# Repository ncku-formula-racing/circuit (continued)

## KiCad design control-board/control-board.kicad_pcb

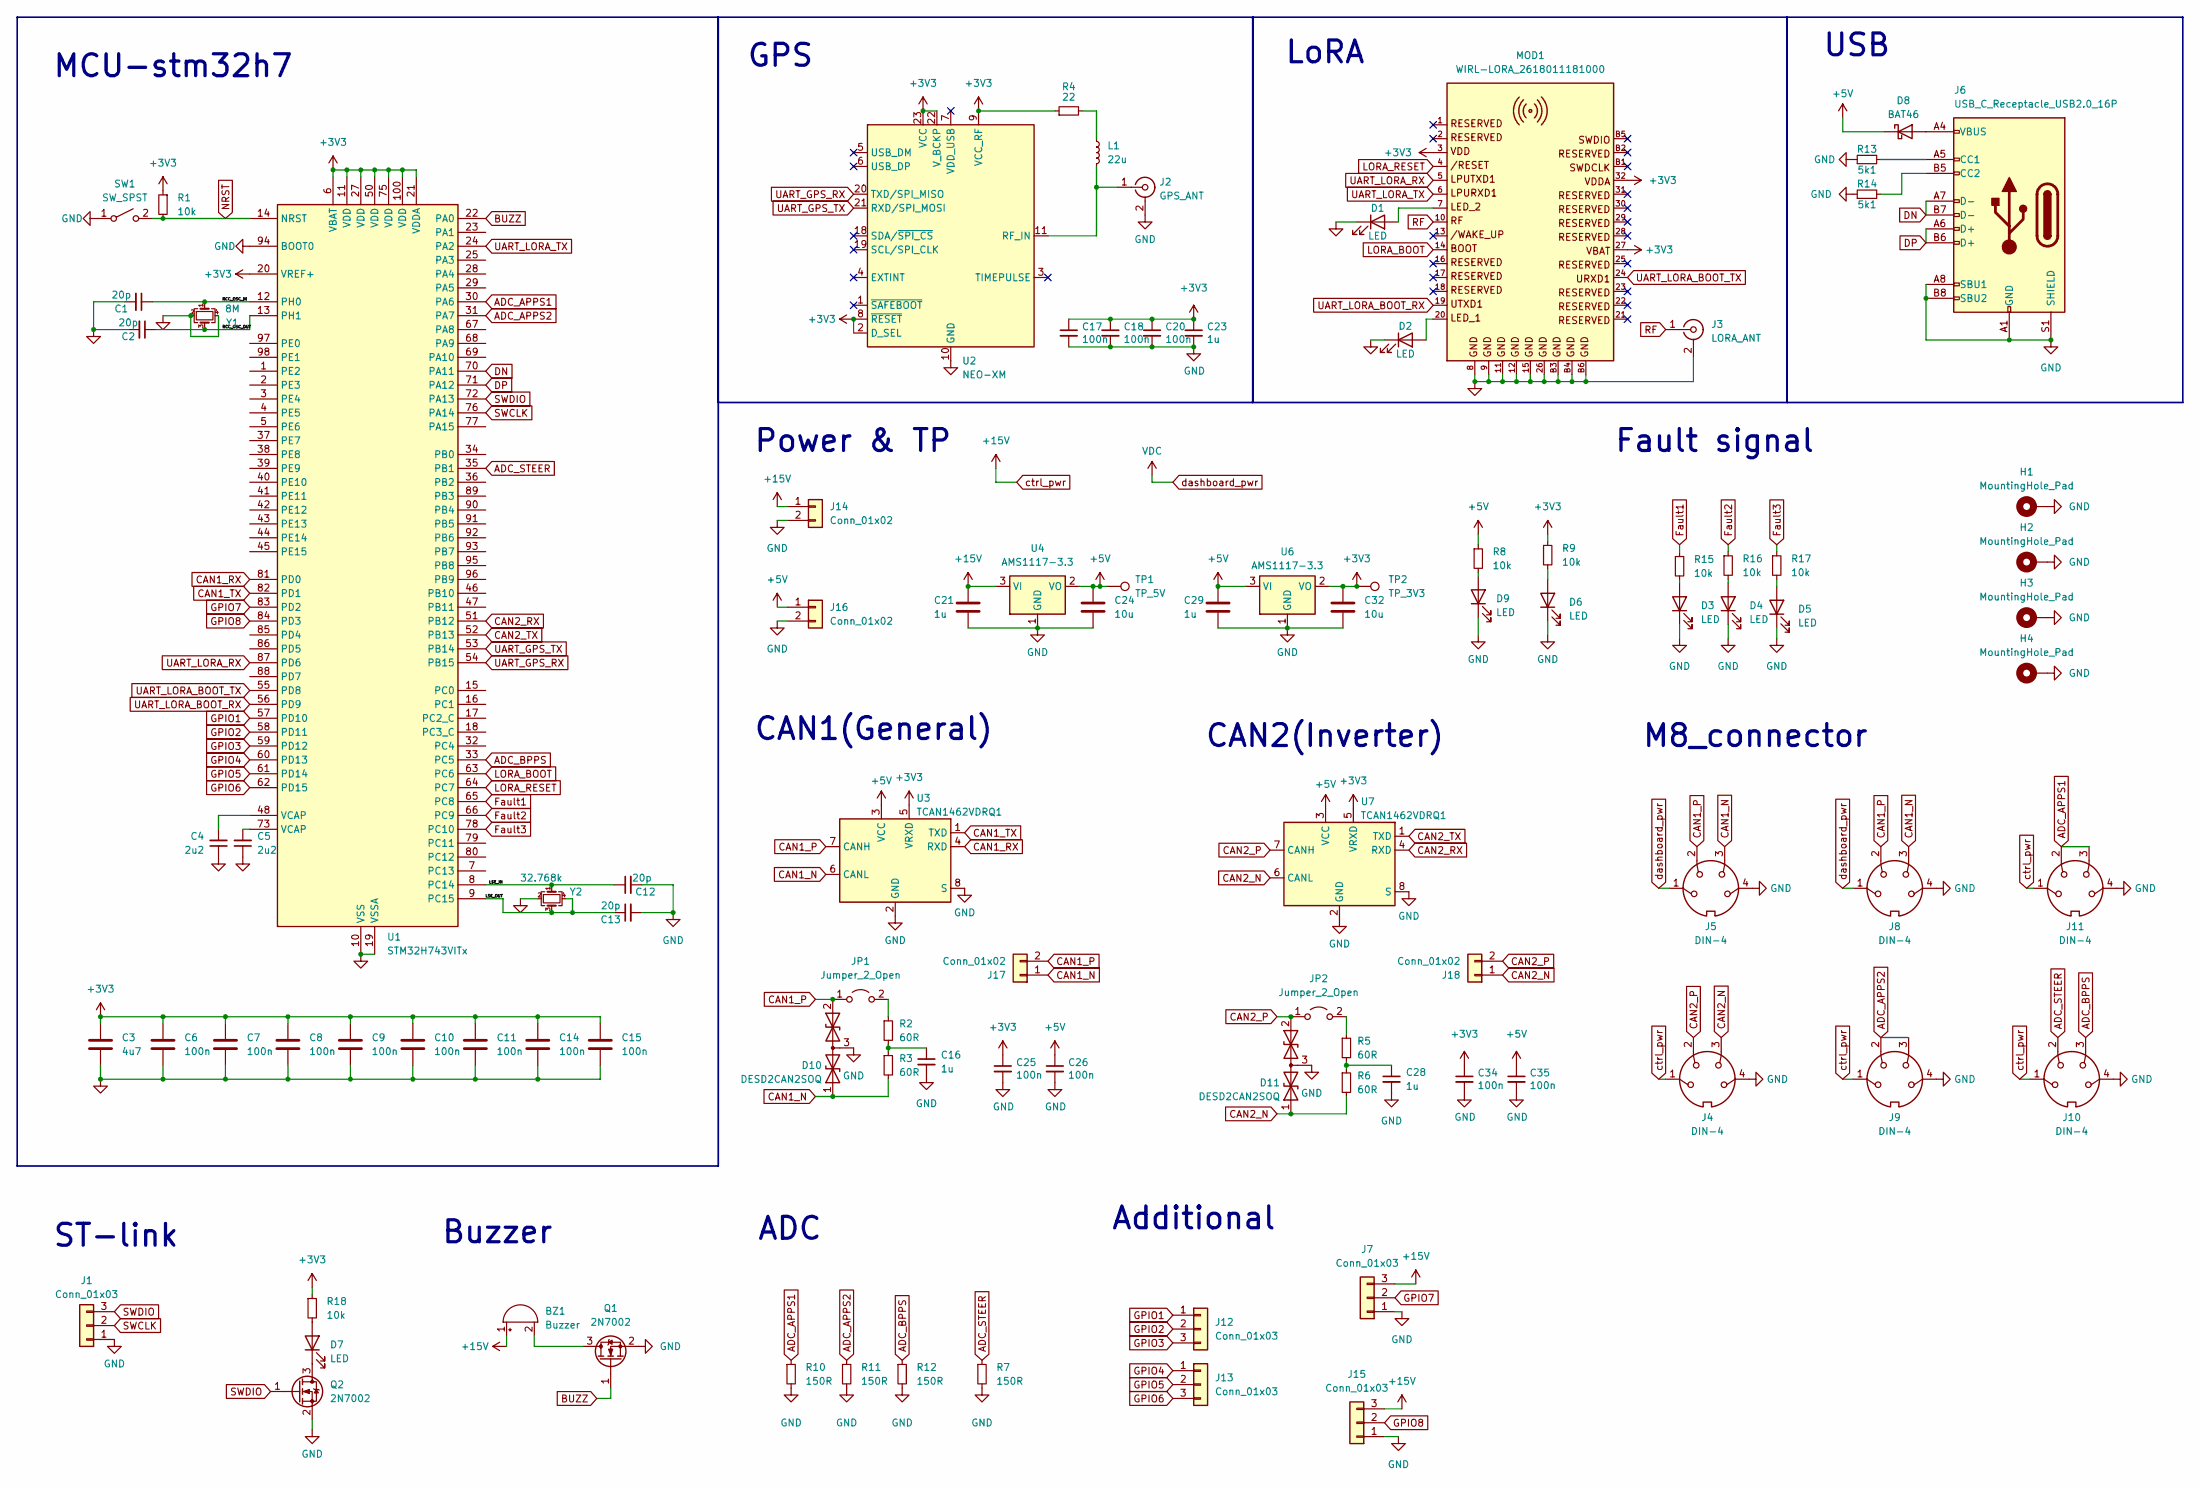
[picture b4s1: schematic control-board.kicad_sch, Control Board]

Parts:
BZ1: Buzzer; Buzzer_15x7.5RM7.6
C1, C2, C12, C13: 20p; C_0603_1608Metric
C3: 4u7; C_0805_2012Metric
C4, C5: 2u2; C_0805_2012Metric
C6, C7, C8, C9, C10, C11, C14, C15, C17, C18, C20, C25, C26, C34, C35: 100n; C_0603_1608Metric
C16, C21, C23, C28, C29: 1u; C_0603_1608Metric
C24, C32: 10u; C_0805_2012Metric
D1, D2, D3, D4, D5, D6, D7, D9: LED; LED_0805_2012Metric
D8: BAT46; D_SOD-123
D10, D11: DESD2CAN2SOQ; TSOT-23
H1, H2, H3, H4: MountingHole_Pad; MountingHole_3.2mm_M3_ISO14580_Pad
J1, J12, J13: Conn_01x03; PinHeader_1x03_P2.54mm_Vertical
J2: GPS_ANT; SMA_Amphenol_901-143_Horizontal
J3: LORA_ANT; SMA_Amphenol_901-143_Horizontal
J4, J5, J8, J9, J10, J11: DIN-4; M8_Female_Conn_Panel_P4_90
J6: USB_C_Receptacle_USB2.0_16P; USB_C_Receptacle_HRO_TYPE-C-31-M-12
J7, J15: Conn_01x03; JST_XH_B3B-XH-A_1x03_P2.50mm_Vertical
J14, J16, J17, J18: Conn_01x02; PinHeader_1x02_P2.54mm_Vertical
JP1, JP2: Jumper_2_Open; TestPoint_2Pads_Pitch2.54mm_Drill0.8mm
L1: 22u; L_0805_2012Metric
MOD1: WIRL-LORA_2618011181000; WE-FP-8
Q1, Q2: 2N7002; SOT-23
R1, R8, R9, R15, R16, R17, R18: 10k; R_0603_1608Metric
R2, R3, R5, R6: 60R; R_0603_1608Metric
R4: 22; R_0603_1608Metric
R7, R10, R11, R12: 150R; R_0603_1608Metric
R13, R14: 5k1; R_0603_1608Metric
SW1: SW_SPST; SW_SPST_FSMSM
TP1: TP_5V; TestPoint_THTPad_D1.5mm_Drill0.7mm
TP2: TP_3V3; TestPoint_THTPad_D1.5mm_Drill0.7mm
U1: STM32H743VITx; LQFP-100_14x14mm_P0.5mm
U2: NEO-XM; ublox_NEO
U3, U7: TCAN1462VDRQ1; SOIC-8_3.9x4.9mm_P1.27mm
U4, U6: AMS1117-3.3; SOT-223-3_TabPin2
Y1: 8M; Crystal_SMD_SeikoEpson_FA238-4Pin_3.2x2.5mm
Y2: 32.768k; Crystal_SMD_SeikoEpson_FA238-4Pin_3.2x2.5mm

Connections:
+3V3: C3.1, C6.1, C7.1, C8.1, C9.1, C10.1, C11.1, C14.1, C15.1, C17.1, C18.1, C20.1, C23.1, C25.1, C32.1, C34.1, MOD1.3, MOD1.27, MOD1.32, R1.1, R4.1, R9.1, R18.1, TP2.1, U1.6 (VBAT), U1.11 (VDD), U1.20 (VREF+), U1.21 (VDDA), U1.27 (VDD), U1.50 (VDD), U1.75 (VDD), U1.100 (VDD), U2.2 (D_SEL), U2.8 (~RESET), U2.9 (VCC_RF), U2.22 (V_BCKP), U2.23 (VCC), U3.5 (VRXD), U6.2 (VO), U7.5 (VRXD)
+5V: C24.1, C26.1, C29.1, C35.1, D8.1 (K), J16.1, R8.1, TP1.1, U3.3 (VCC), U4.2 (VO), U6.3 (VI), U7.3 (VCC)
/LSE_IN: C12.1, U1.8 (PC14), Y2.1
/LSE_OUT: C13.1, U1.9 (PC15), Y2.3, Y2.4
/RCC_OSC_IN: C1.1, U1.12 (PH0), Y1.1
/RCC_OSC_OUT: C2.1, U1.13 (PH1), Y1.3
ADC_APPS1: J11.2, J11.3, R10.1, U1.30 (PA6)
ADC_APPS2: J9.2, J9.3, R11.1, U1.31 (PA7)
ADC_BPPS: J10.3, R12.1, U1.33 (PC5)
ADC_STEER: J10.2, R7.1, U1.35 (PB1)
BUZZ: Q1.1 (G), U1.22 (PA0)
CAN1_N: D10.1 (A1), J5.3, J8.3, J17.1, R3.2, U3.6 (CANL)
CAN1_P: D10.2 (A2), J5.2, J8.2, J17.2, JP1.1 (A), U3.7 (CANH)
CAN1_RX: U1.81 (PD0), U3.4 (RXD)
CAN1_TX: U1.82 (PD1), U3.1 (TXD)
CAN2_N: D11.1 (A1), J4.3, J18.1, R6.2, U7.6 (CANL)
CAN2_P: D11.2 (A2), J4.2, J18.2, JP2.1 (A), U7.7 (CANH)
CAN2_RX: U1.51 (PB12), U7.4 (RXD)
CAN2_TX: U1.52 (PB13), U7.1 (TXD)
DN: J6.A7 (D-), J6.B7 (D-), U1.70 (PA11)
DP: J6.A6 (D+), J6.B6 (D+), U1.71 (PA12)
Fault1: R15.1, U1.65 (PC8)
Fault2: R16.1, U1.66 (PC9)
Fault3: R17.1, U1.78 (PC10)
GND: C1.2, C2.2, C3.2, C4.1, C5.1, C6.2, C7.2, C8.2, C9.2, C10.2, C11.2, C12.2, C13.2, C14.2, C15.2, C16.2, C17.2, C18.2, C20.2, C21.2, C23.2, C24.2, C25.2, C26.2, C28.2, C29.2, C32.2, C34.2, C35.2, D1.1 (K), D2.1 (K), D3.1 (K), D4.1 (K), D5.1 (K), D6.1 (K), D9.1 (K), D10.3 (common), D11.3 (common), H1.1, H2.1, H3.1, H4.1, J1.1, J2.2 (Ext), J3.2 (Ext), J4.4, J5.4, J6.A1 (GND), J6.A8 (SBU1), J6.A12 (GND), J6.B1 (GND), J6.B8 (SBU2), J6.B12 (GND), J6.S1 (SHIELD), J7.1, J8.4, J9.4, J10.4, J11.4, J14.2, J15.1, J16.2, MOD1.8, MOD1.9, MOD1.11, MOD1.12, MOD1.15, MOD1.26, MOD1.B3, MOD1.B4, MOD1.B6, Q1.2 (S), Q2.2 (S), R7.2, R10.2, R11.2, R12.2, R13.1, R14.1, SW1.1 (A), U1.10 (VSS), U1.19 (VSSA), U1.26 (VSS), U1.49 (VSS), U1.74 (VSS), U1.94 (BOOT0), U1.99 (VSS), U2.10 (GND), U2.12 (GND), U2.13 (GND), U2.24 (GND), U3.2 (GND), U3.8 (S), U4.1 (GND), U6.1 (GND), U7.2 (GND), U7.8 (S), Y1.2, Y1.4, Y2.2
GPIO1: J12.1, U1.57 (PD10)
GPIO2: J12.2, U1.58 (PD11)
GPIO3: J12.3, U1.59 (PD12)
GPIO4: J13.1, U1.60 (PD13)
GPIO5: J13.2, U1.61 (PD14)
GPIO6: J13.3, U1.62 (PD15)
GPIO7: J7.2, U1.83 (PD2)
GPIO8: J15.2, U1.84 (PD3)
LORA_BOOT: MOD1.14, U1.63 (PC6)
LORA_RESET: MOD1.4, U1.64 (PC7)
NRST: R1.2, SW1.2 (B), U1.14 (NRST)
unnamed: BZ1.2 (-), Q1.3 (D)
unnamed: C4.2, U1.48 (VCAP)
unnamed: C5.2, U1.73 (VCAP)
unnamed: C16.1, R2.2, R3.1
unnamed: C28.1, R5.2, R6.1
unnamed: D1.2 (A), MOD1.7
unnamed: D2.2 (A), MOD1.20
unnamed: D3.2 (A), R15.2
unnamed: D4.2 (A), R16.2
unnamed: D5.2 (A), R17.2
unnamed: D6.2 (A), R9.2
unnamed: D7.2 (A), R18.2
unnamed: D7.1 (K), Q2.3 (D)
unnamed: D8.2 (A), J6.A4 (VBUS), J6.A9 (VBUS), J6.B4 (VBUS), J6.B9 (VBUS)
unnamed: D9.2 (A), R8.2
unnamed: J2.1 (In), L1.2, U2.11 (RF_IN)
unnamed: J6.A5 (CC1), R13.2
unnamed: J6.B5 (CC2), R14.2
unnamed: JP1.2 (B), R2.1
unnamed: JP2.2 (B), R5.1
unnamed: L1.1, R4.2
RF: J3.1 (In), MOD1.10
SWCLK: J1.2, U1.76 (PA14)
SWDIO: J1.3, Q2.1 (G), U1.72 (PA13)
UART_GPS_RX: U1.54 (PB15), U2.20 (TXD/SPI_MISO)
UART_GPS_TX: U1.53 (PB14), U2.21 (RXD/SPI_MOSI)
UART_LORA_BOOT_RX: MOD1.19, U1.56 (PD9)
UART_LORA_BOOT_TX: MOD1.24, U1.55 (PD8)
UART_LORA_RX: MOD1.5, U1.87 (PD6)
UART_LORA_TX: MOD1.6, U1.24 (PA2)
ctrl_pwr: BZ1.1 (+), C21.1, J4.1, J7.3, J9.1, J10.1, J11.1, J14.1, J15.3, U4.3 (VI)
dashboard_pwr: J5.1, J8.1

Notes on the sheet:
GPS
Fault signal
CAN1(General)
ADC
ST-link
LoRA
CAN2(Inverter)
Power & TP
MCU-stm32h7
USB
M8_connector
Additional
Buzzer

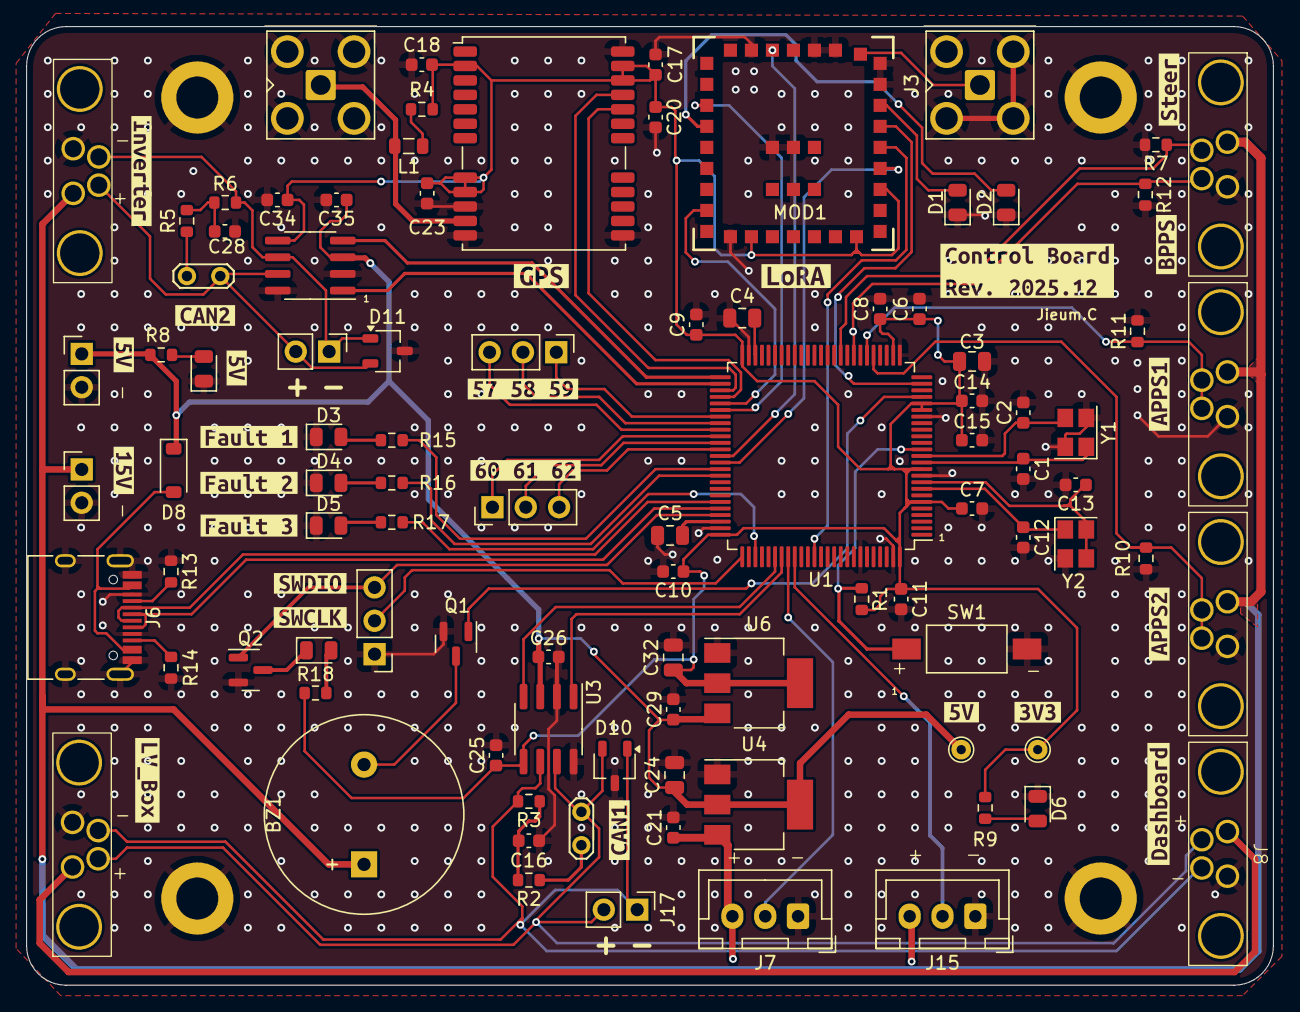
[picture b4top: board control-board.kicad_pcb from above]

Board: 2 copper layers, 94.9 x 73.0 mm, 122 parts (0 on the bottom side), 68 nets.

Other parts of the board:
kibuzzard-68C81B7C: G***; kibuzzard-68C81B7C
kibuzzard-68C81B8D: G***; kibuzzard-68C81B8D
kibuzzard-68C81B55: G***; kibuzzard-68C81B55
kibuzzard-68C81B65: G***; kibuzzard-68C81B65
kibuzzard-68C81BE5: G***; kibuzzard-68C81BE5
kibuzzard-68C81C0C: G***; kibuzzard-68C81C0C
kibuzzard-68C81C5A: G***; kibuzzard-68C81C5A
kibuzzard-68C81C70: G***; kibuzzard-68C81C70
kibuzzard-68C831DA: G***; kibuzzard-68C831DA
kibuzzard-68C831E3: G***; kibuzzard-68C831E3
kibuzzard-68C836E4: G***; kibuzzard-68C836E4
kibuzzard-68C836FB: G***; kibuzzard-68C836FB
kibuzzard-68C839A7: G***; kibuzzard-68C839A7
kibuzzard-68C839C6: G***; kibuzzard-68C839C6
kibuzzard-68C8462F: G***; kibuzzard-68C8462F
kibuzzard-68CAD5A3: G***; kibuzzard-68CAD5A3
kibuzzard-68CAD58E: G***; kibuzzard-68CAD58E
kibuzzard-68DAC5A1: G***; kibuzzard-68DAC5A1
kibuzzard-68DAC5B3: G***; kibuzzard-68DAC5B3
kibuzzard-68DAC17B: G***; kibuzzard-68DAC17B
kibuzzard-68E0D6FC, kibuzzard-68E0D6FC#2: G***; kibuzzard-68E0D6FC
kibuzzard-6932874B: G***; kibuzzard-6932874B
kibuzzard-6932882F: G***; kibuzzard-6932882F

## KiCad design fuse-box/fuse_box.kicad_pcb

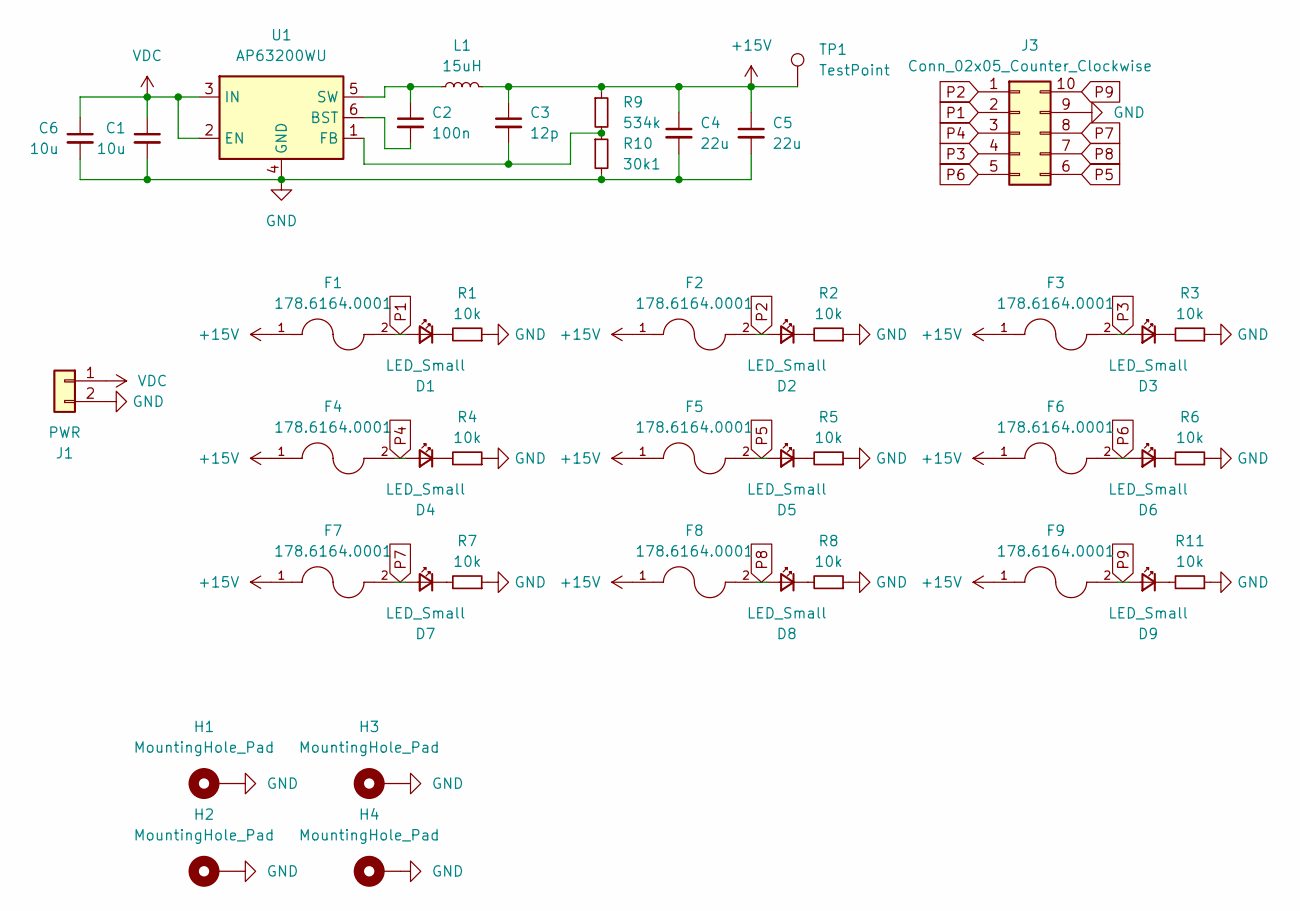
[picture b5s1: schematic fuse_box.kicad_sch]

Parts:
C1, C6: 10u; C_0805_2012Metric
C2: 100n; C_0603_1608Metric
C3: 12p; C_0603_1608Metric
C4, C5: 22u; C_0805_2012Metric
D1, D2, D3, D4, D5, D6, D7, D8, D9: LED_Small; LED_0805_2012Metric
F1, F2, F3, F4, F5, F6, F7, F8, F9: 178.6164.0001; LITTELFUSE_178.6164.0001; PARTREV 06.04.05
H1, H2, H3, H4: MountingHole_Pad; MountingHole_3.2mm_M3_ISO7380_Pad
J1: PWR; AMASS_XT60-M_1x02_P7.20mm_Vertical
J3: Conn_02x05_Counter_Clockwise; PinHeader_2x05_P2.54mm_Vertical
L1: 15uH; L_Coilcraft_XAL6060-XXX
R1, R2, R3, R4, R5, R6, R7, R8, R11: 10k; R_0603_1608Metric
R9: 534k; R_0603_1608Metric
R10: 30k1; R_0603_1608Metric
TP1: TestPoint; TestPoint_THTPad_D1.5mm_Drill0.7mm
U1: AP63200WU; TSOT-23-6

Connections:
+15V: C3.1, C4.1, C5.1, F1.1, F2.1, F3.1, F4.1, F5.1, F6.1, F7.1, F8.1, F9.1, L1.2, R9.1, TP1.1
GND: C1.2, C4.2, C5.2, C6.2, H1.1, H2.1, H3.1, H4.1, J1.2, J3.9, R1.1, R2.1, R3.1, R4.1, R5.1, R6.1, R7.1, R8.1, R10.2, R11.1, U1.4 (GND)
unnamed: D1.1 (K), R1.2
unnamed: D2.1 (K), R2.2
unnamed: D3.1 (K), R3.2
unnamed: D4.1 (K), R4.2
unnamed: D5.1 (K), R5.2
unnamed: D6.1 (K), R6.2
unnamed: D7.1 (K), R7.2
unnamed: D8.1 (K), R8.2
unnamed: D9.1 (K), R11.2
unnamed: C2.2, U1.6 (BST)
unnamed: C3.2, R9.2, R10.1, U1.1 (FB)
unnamed: C2.1, L1.1, U1.5 (SW)
P1: D1.2 (A), F1.2, J3.2
P2: D2.2 (A), F2.2, J3.1
P3: D3.2 (A), F3.2, J3.4
P4: D4.2 (A), F4.2, J3.3
P5: D5.2 (A), F5.2, J3.6
P6: D6.2 (A), F6.2, J3.5
P7: D7.2 (A), F7.2, J3.8
P8: D8.2 (A), F8.2, J3.7
P9: D9.2 (A), F9.2, J3.10
VDC: C1.1, C6.1, J1.1, U1.2 (EN), U1.3 (IN)

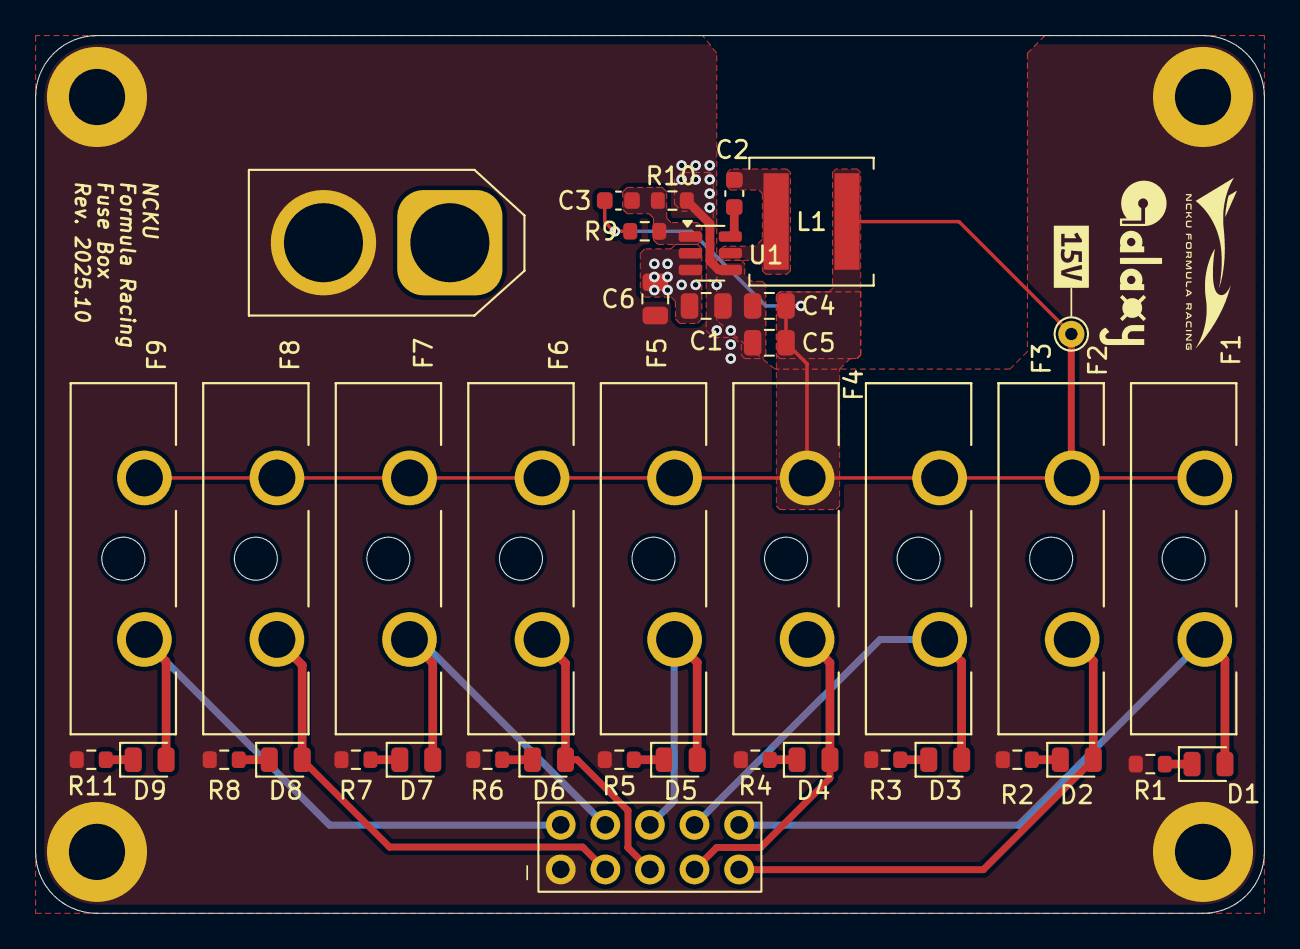
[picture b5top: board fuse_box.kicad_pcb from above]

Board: 2 copper layers, 70.0 x 50.0 mm, 45 parts (1 on the bottom side), 24 nets.

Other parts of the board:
kibuzzard-67D51968: G***; kibuzzard-67D51968

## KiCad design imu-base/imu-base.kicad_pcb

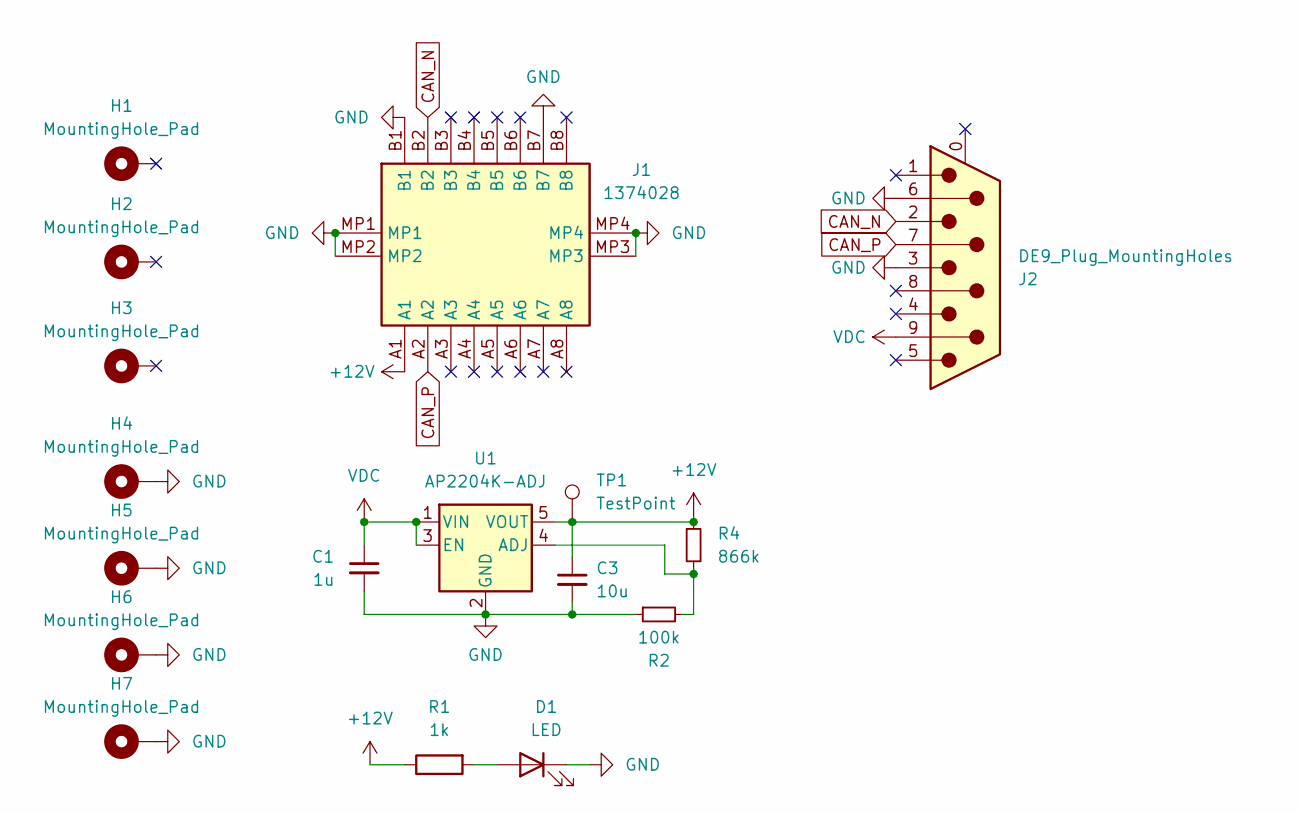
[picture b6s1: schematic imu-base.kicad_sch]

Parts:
C1: 1u; C_0603_1608Metric_Pad1.08x0.95mm_HandSolder
C3: 10u; C_0805_2012Metric_Pad1.18x1.45mm_HandSolder
D1: LED; LED_0805_2012Metric_Pad1.15x1.40mm_HandSolder
H1, H2, H3, H4, H5, H6, H7: MountingHole_Pad; MountingHole_2.2mm_M2_Pad
J1: 1374028; Manufacturer_Part_Number 1374028
J2: DE9_Plug_MountingHoles; DSUB-9_Female_Horizontal_P2.77x2.84mm_EdgePinOffset7.70mm_H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
R1: 1k; R_0603_1608Metric_Pad0.98x0.95mm_HandSolder
R2: 100k; R_0603_1608Metric
R4: 866k; R_0603_1608Metric
TP1: TestPoint; TestPoint_THTPad_D2.0mm_Drill1.0mm
U1: AP2204K-ADJ; SOT-23-5

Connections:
+12V: C3.1, J1.A1, R1.1, R4.1, TP1.1, U1.5 (VOUT)
CAN_N: J1.B2, J2.2
CAN_P: J1.A2, J2.7
GND: C1.2, C3.2, D1.1 (K), H4.1, H5.1, H6.1, H7.1, J1.B1, J1.B7, J1.MP1, J1.MP2, J1.MP3, J1.MP4, J2.3, J2.6, R2.1, U1.2 (GND)
unnamed: D1.2 (A), R1.2
unnamed: R2.2, R4.2, U1.4 (ADJ)
VDC: C1.1, J2.9, U1.1 (VIN), U1.3 (EN)

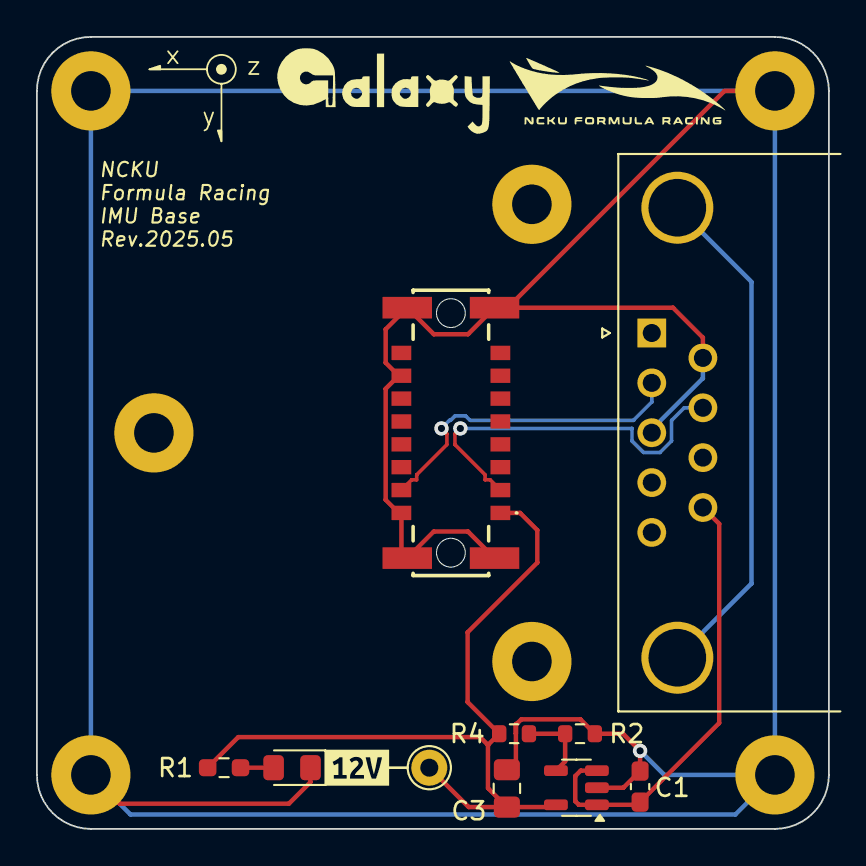
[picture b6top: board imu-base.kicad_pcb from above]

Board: 2 copper layers, 44.0 x 44.0 mm, 18 parts (0 on the bottom side), 7 nets.

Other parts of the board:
kibuzzard-679C6BCB: G***; kibuzzard-679C6BCB

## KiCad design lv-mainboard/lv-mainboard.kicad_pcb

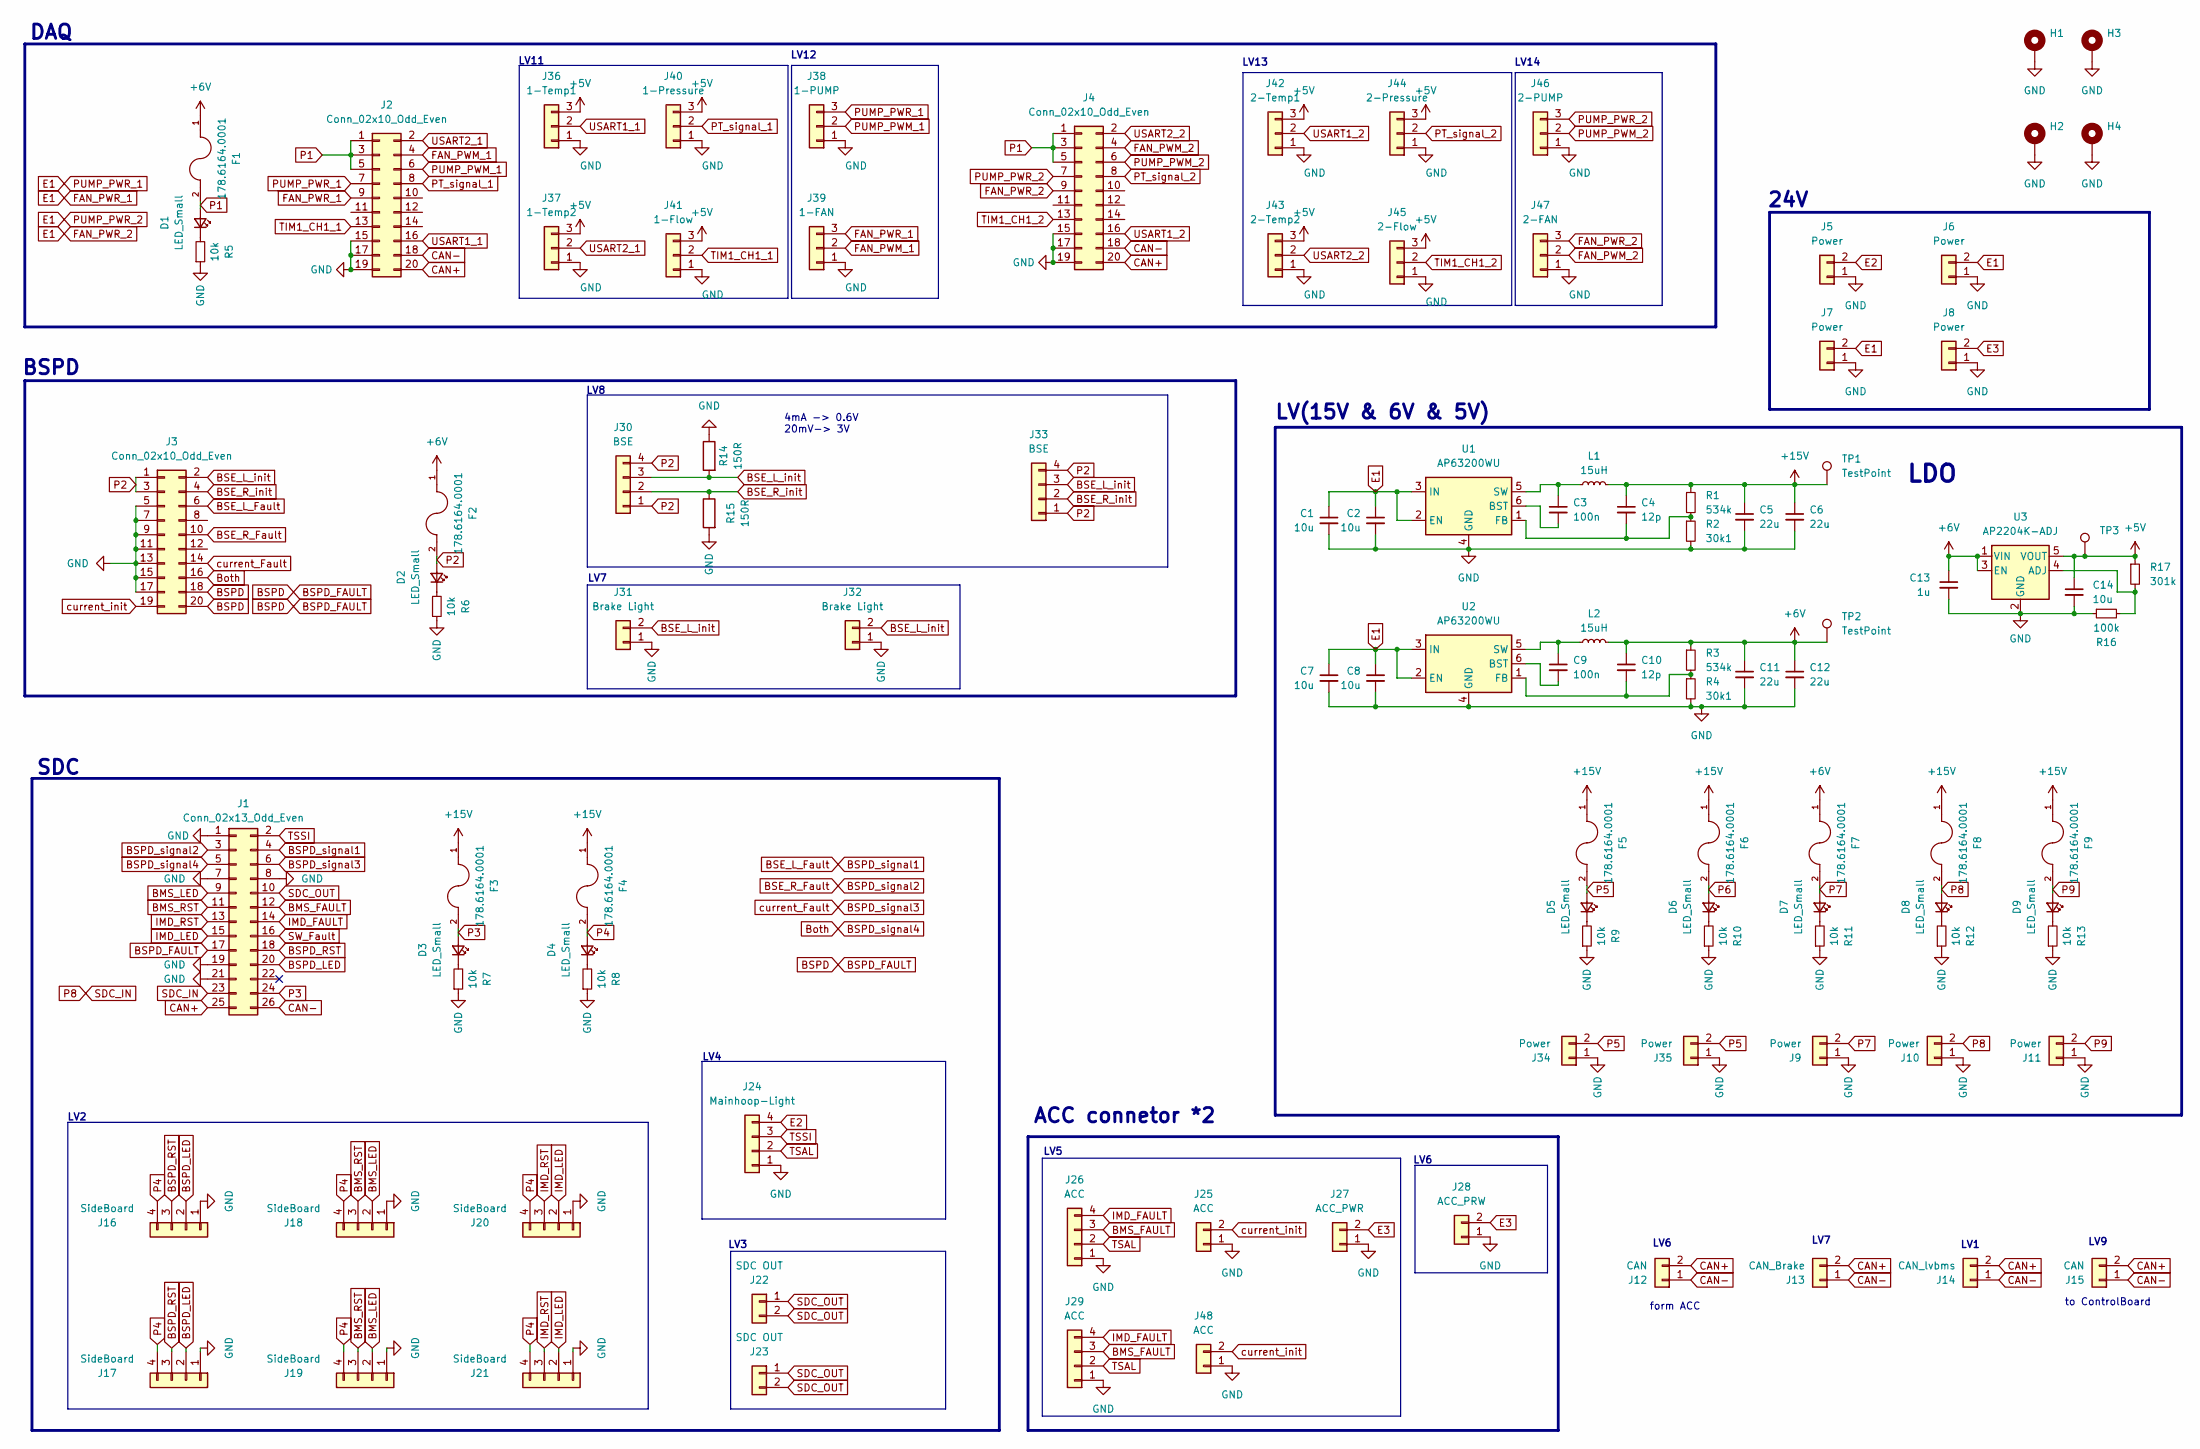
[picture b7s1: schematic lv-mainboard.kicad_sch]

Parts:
C1, C2, C7, C8, C14: 10u; C_0805_2012Metric
C3, C9: 100n; C_0603_1608Metric
C4, C10: 12p; C_0603_1608Metric
C5, C6, C11, C12: 22u; C_0805_2012Metric
C13: 1u; C_0603_1608Metric
D1, D2, D3, D4, D5, D6, D7, D8, D9: LED_Small; LED_0805_2012Metric
F1, F2, F3, F4, F5, F6, F7, F8, F9: 178.6164.0001; LITTELFUSE_178.6164.0001; PARTREV 06.04.05
H1, H2, H3, H4: MountingHole_Pad; MountingHole_4.3mm_M4_ISO7380_Pad
J1: Conn_02x13_Odd_Even; PinSocket_2x13_P2.54mm_Vertical
J2, J3, J4: Conn_02x10_Odd_Even; PinSocket_2x10_P2.54mm_Vertical
J5, J6, J7, J8: Power; JST_XH_S2B-XH-A-1_1x02_P2.50mm_Horizontal
J9, J10, J11, J34, J35: Power; JST_XH_B2B-XH-A_1x02_P2.50mm_Vertical
J12, J15: CAN; JST_XH_B2B-XH-A_1x02_P2.50mm_Vertical
J13: CAN_Brake; JST_XH_B2B-XH-A_1x02_P2.50mm_Vertical
J14: CAN_lvbms; JST_XH_B2B-XH-A_1x02_P2.50mm_Vertical
J16, J17, J18, J19, J20, J21: SideBoard; JST_XH_B4B-XH-A_1x04_P2.50mm_Vertical
J22, J23: SDC OUT; AMASS_XT60-M_1x02_P7.20mm_Vertical
J24: Mainhoop-Light; JST_XH_B4B-XH-A_1x04_P2.50mm_Vertical
J25, J48: ACC; JST_XH_B2B-XH-A_1x02_P2.50mm_Vertical
J26, J29: ACC; JST_XH_B4B-XH-A_1x04_P2.50mm_Vertical
J27: ACC_PWR; JST_XH_B2B-XH-A_1x02_P2.50mm_Vertical
J28: ACC_PRW; JST_XH_B2B-XH-A_1x02_P2.50mm_Vertical
J30, J33: BSE; JST_XH_B4B-XH-A_1x04_P2.50mm_Vertical
J31, J32: Brake Light; JST_XH_B2B-XH-A_1x02_P2.50mm_Vertical
J36: 1-Temp1; JST_XH_B3B-XH-A_1x03_P2.50mm_Vertical
J37: 1-Temp2; JST_XH_B3B-XH-A_1x03_P2.50mm_Vertical
J38: 1-PUMP; JST_XH_B3B-XH-A_1x03_P2.50mm_Vertical
J39: 1-FAN; JST_XH_B3B-XH-A_1x03_P2.50mm_Vertical
J40: 1-Pressure; JST_XH_B3B-XH-A_1x03_P2.50mm_Vertical
J41: 1-Flow; JST_XH_B3B-XH-A_1x03_P2.50mm_Vertical
J42: 2-Temp1; JST_XH_B3B-XH-A_1x03_P2.50mm_Vertical
J43: 2-Temp2; JST_XH_B3B-XH-A_1x03_P2.50mm_Vertical
J44: 2-Pressure; JST_XH_B3B-XH-A_1x03_P2.50mm_Vertical
J45: 2-Flow; JST_XH_B3B-XH-A_1x03_P2.50mm_Vertical
J46: 2-PUMP; JST_XH_B3B-XH-A_1x03_P2.50mm_Vertical
J47: 2-FAN; JST_XH_B3B-XH-A_1x03_P2.50mm_Vertical
L1, L2: 15uH; L_Coilcraft_XAL6060-XXX
R1, R3: 534k; R_0603_1608Metric
R2, R4: 30k1; R_0603_1608Metric
R5, R6, R7, R8, R9, R10, R11, R12, R13: 10k; R_0603_1608Metric
R14, R15: 150R; R_0603_1608Metric
R16: 100k; R_0603_1608Metric
R17: 301k; R_0603_1608Metric
TP1, TP2, TP3: TestPoint; TestPoint_THTPad_D1.5mm_Drill0.7mm
U1, U2: AP63200WU; TSOT-23-6
U3: AP2204K-ADJ; SOT-23-5

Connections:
+5V: C14.1, J36.3, J37.3, J40.3, J41.3, J42.3, J43.3, J44.3, J45.3, R17.1, TP3.1, U3.5 (VOUT)
+6V: C10.1, C11.1, C12.1, C13.1, F1.1, F2.1, F7.1, L2.2, R3.1, TP2.1, U3.1 (VIN), U3.3 (EN)
+15V: C4.1, C5.1, C6.1, F3.1, F4.1, F5.1, F6.1, F8.1, F9.1, L1.2, R1.1, TP1.1
BMS_FAULT: J1.12, J26.3, J29.3
BMS_LED: J1.9, J18.2, J19.2
BMS_RST: J1.11, J18.3, J19.3
BSE_L_Fault: J1.4, J3.6
BSE_L_init: J3.2, J30.3, J31.2, J32.2, J33.3, R14.2
BSE_R_Fault: J1.3, J3.10
BSE_R_init: J3.4, J30.2, J33.2, R15.1
BSPD: J1.17, J3.18, J3.20
BSPD_LED: J1.20, J16.2, J17.2
BSPD_RST: J1.18, J16.3, J17.3
BSPD_signal3: J1.6, J3.14
BSPD_signal4: J1.5, J3.16
CAN+: J1.25, J2.20, J4.20, J12.2, J13.2, J14.2, J15.2
CAN-: J1.26, J2.18, J4.18, J12.1, J13.1, J14.1, J15.1
E1: C1.1, C2.1, C7.1, C8.1, J2.7, J2.9, J4.7, J4.9, J6.2, J7.2, J38.3, J39.3, J46.3, J47.3, U1.2 (EN), U1.3 (IN), U2.2 (EN), U2.3 (IN)
E2: J5.2, J24.4
E3: J8.2, J27.2, J28.2
FAN_PWM_1: J2.4, J39.2
FAN_PWM_2: J4.4, J47.2
GND: C1.2, C2.2, C5.2, C6.2, C7.2, C8.2, C11.2, C12.2, C13.2, C14.2, H1.1, H2.1, H3.1, H4.1, J1.1, J1.7, J1.8, J1.19, J1.21, J2.15, J2.17, J2.19, J3.5, J3.7, J3.9, J3.11, J3.13, J3.15, J3.17, J4.15, J4.17, J4.19, J5.1, J6.1, J7.1, J8.1, J9.1, J10.1, J11.1, J16.1, J17.1, J18.1, J19.1, J20.1, J21.1, J24.1, J25.1, J26.1, J27.1, J28.1, J29.1, J31.1, J32.1, J34.1, J35.1, J36.1, J37.1, J38.1, J39.1, J40.1, J41.1, J42.1, J43.1, J44.1, J45.1, J46.1, J47.1, J48.1, R2.2, R4.2, R5.1, R6.1, R7.1, R8.1, R9.1, R10.1, R11.1, R12.1, R13.1, R14.1, R15.2, R16.1, U1.4 (GND), U2.4 (GND), U3.2 (GND); also elsewhere on the board
IMD_FAULT: J1.14, J26.4, J29.4
IMD_LED: J1.15, J20.2, J21.2
IMD_RST: J1.13, J20.3, J21.3
unnamed: D1.1 (K), R5.2
unnamed: D2.1 (K), R6.2
unnamed: D3.1 (K), R7.2
unnamed: D4.1 (K), R8.2
unnamed: D5.1 (K), R9.2
unnamed: D6.1 (K), R10.2
unnamed: D7.1 (K), R11.2
unnamed: D8.1 (K), R12.2
unnamed: D9.1 (K), R13.2
unnamed: C3.2, U1.6 (BST)
unnamed: C4.2, R1.2, R2.1, U1.1 (FB)
unnamed: C3.1, L1.1, U1.5 (SW)
unnamed: C9.2, U2.6 (BST)
unnamed: C10.2, R3.2, R4.1, U2.1 (FB)
unnamed: C9.1, L2.1, U2.5 (SW)
unnamed: R16.2, R17.2, U3.4 (ADJ)
P1: D1.2 (A), F1.2, J2.1, J2.3, J2.5, J4.1, J4.3, J4.5
P2: D2.2 (A), F2.2, J3.1, J3.3, J30.1, J30.4, J33.1, J33.4
P3: D3.2 (A), F3.2, J1.24
P4: D4.2 (A), F4.2, J16.4, J17.4, J18.4, J19.4, J20.4, J21.4
P5: D5.2 (A), F5.2, J34.2, J35.2
P6: D6.2 (A), F6.2
P7: D7.2 (A), F7.2, J9.2
P8: D8.2 (A), F8.2, J1.23, J10.2
P9: D9.2 (A), F9.2, J11.2
PT_signal_1: J2.8, J40.2
PT_signal_2: J4.8, J44.2
PUMP_PWM_1: J2.6, J38.2
PUMP_PWM_2: J4.6, J46.2
SDC_OUT: J1.10, J22.1, J22.2, J23.1, J23.2
SW_Fault: J1.16
TIM1_CH1_1: J2.13, J41.2
TIM1_CH1_2: J4.13, J45.2
TSAL: J24.2, J26.2, J29.2
TSSI: J1.2, J24.3
USART1_1: J2.16, J36.2
USART1_2: J4.16, J42.2
USART2_1: J2.2, J37.2
USART2_2: J4.2, J43.2
current_init: J3.19, J25.2, J48.2

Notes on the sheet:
4mA -> 0.6V 20mV-> 3V
to ControlBoard
LV6
LV(15V & 6V & 5V)
BSPD
LV4
form ACC
LV3
LDO
LV7
LV12
LV1
DAQ
LV8
ACC connetor *2
LV14
24V
LV2
SDC
LV9
LV13
LV5
LV11
